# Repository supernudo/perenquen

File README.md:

# Perenquen

Robot de laberinto o micromouse.

Perenquén es mi primer robot de laberinto. Tiene una tracción diferencial de 4 ruedas diseñada para acelerar en recta a 10m/s/s y alcanza una velocidad de 3m/s. La posición de su centro de masa le permite hacer giros precisos sobre sus ruedas delanteras sin derrapar, a pesar de tener 4 ruedas. Para controlar su velocidad y posición utiliza encoders magnéticos. Durante las curvas utiliza un giroscopo para girar con precisión, independientemente de si derrapan las ruedas. Además, utiliza 4 sensores infrarrojos (2 delanteros y 2 diagonales) para navegar por el laberinto.

## Autor

Javier Baliñas Santos

## Licencia

Todos estos productos están liberados mediante [Creative Commons Attribution-ShareAlike 4.0 International License](http://creativecommons.org/licenses/by-sa/4.0/).  
*All these products are released under [Creative Commons Attribution-ShareAlike 4.0 International License](http://creativecommons.org/licenses/by-sa/4.0/).*

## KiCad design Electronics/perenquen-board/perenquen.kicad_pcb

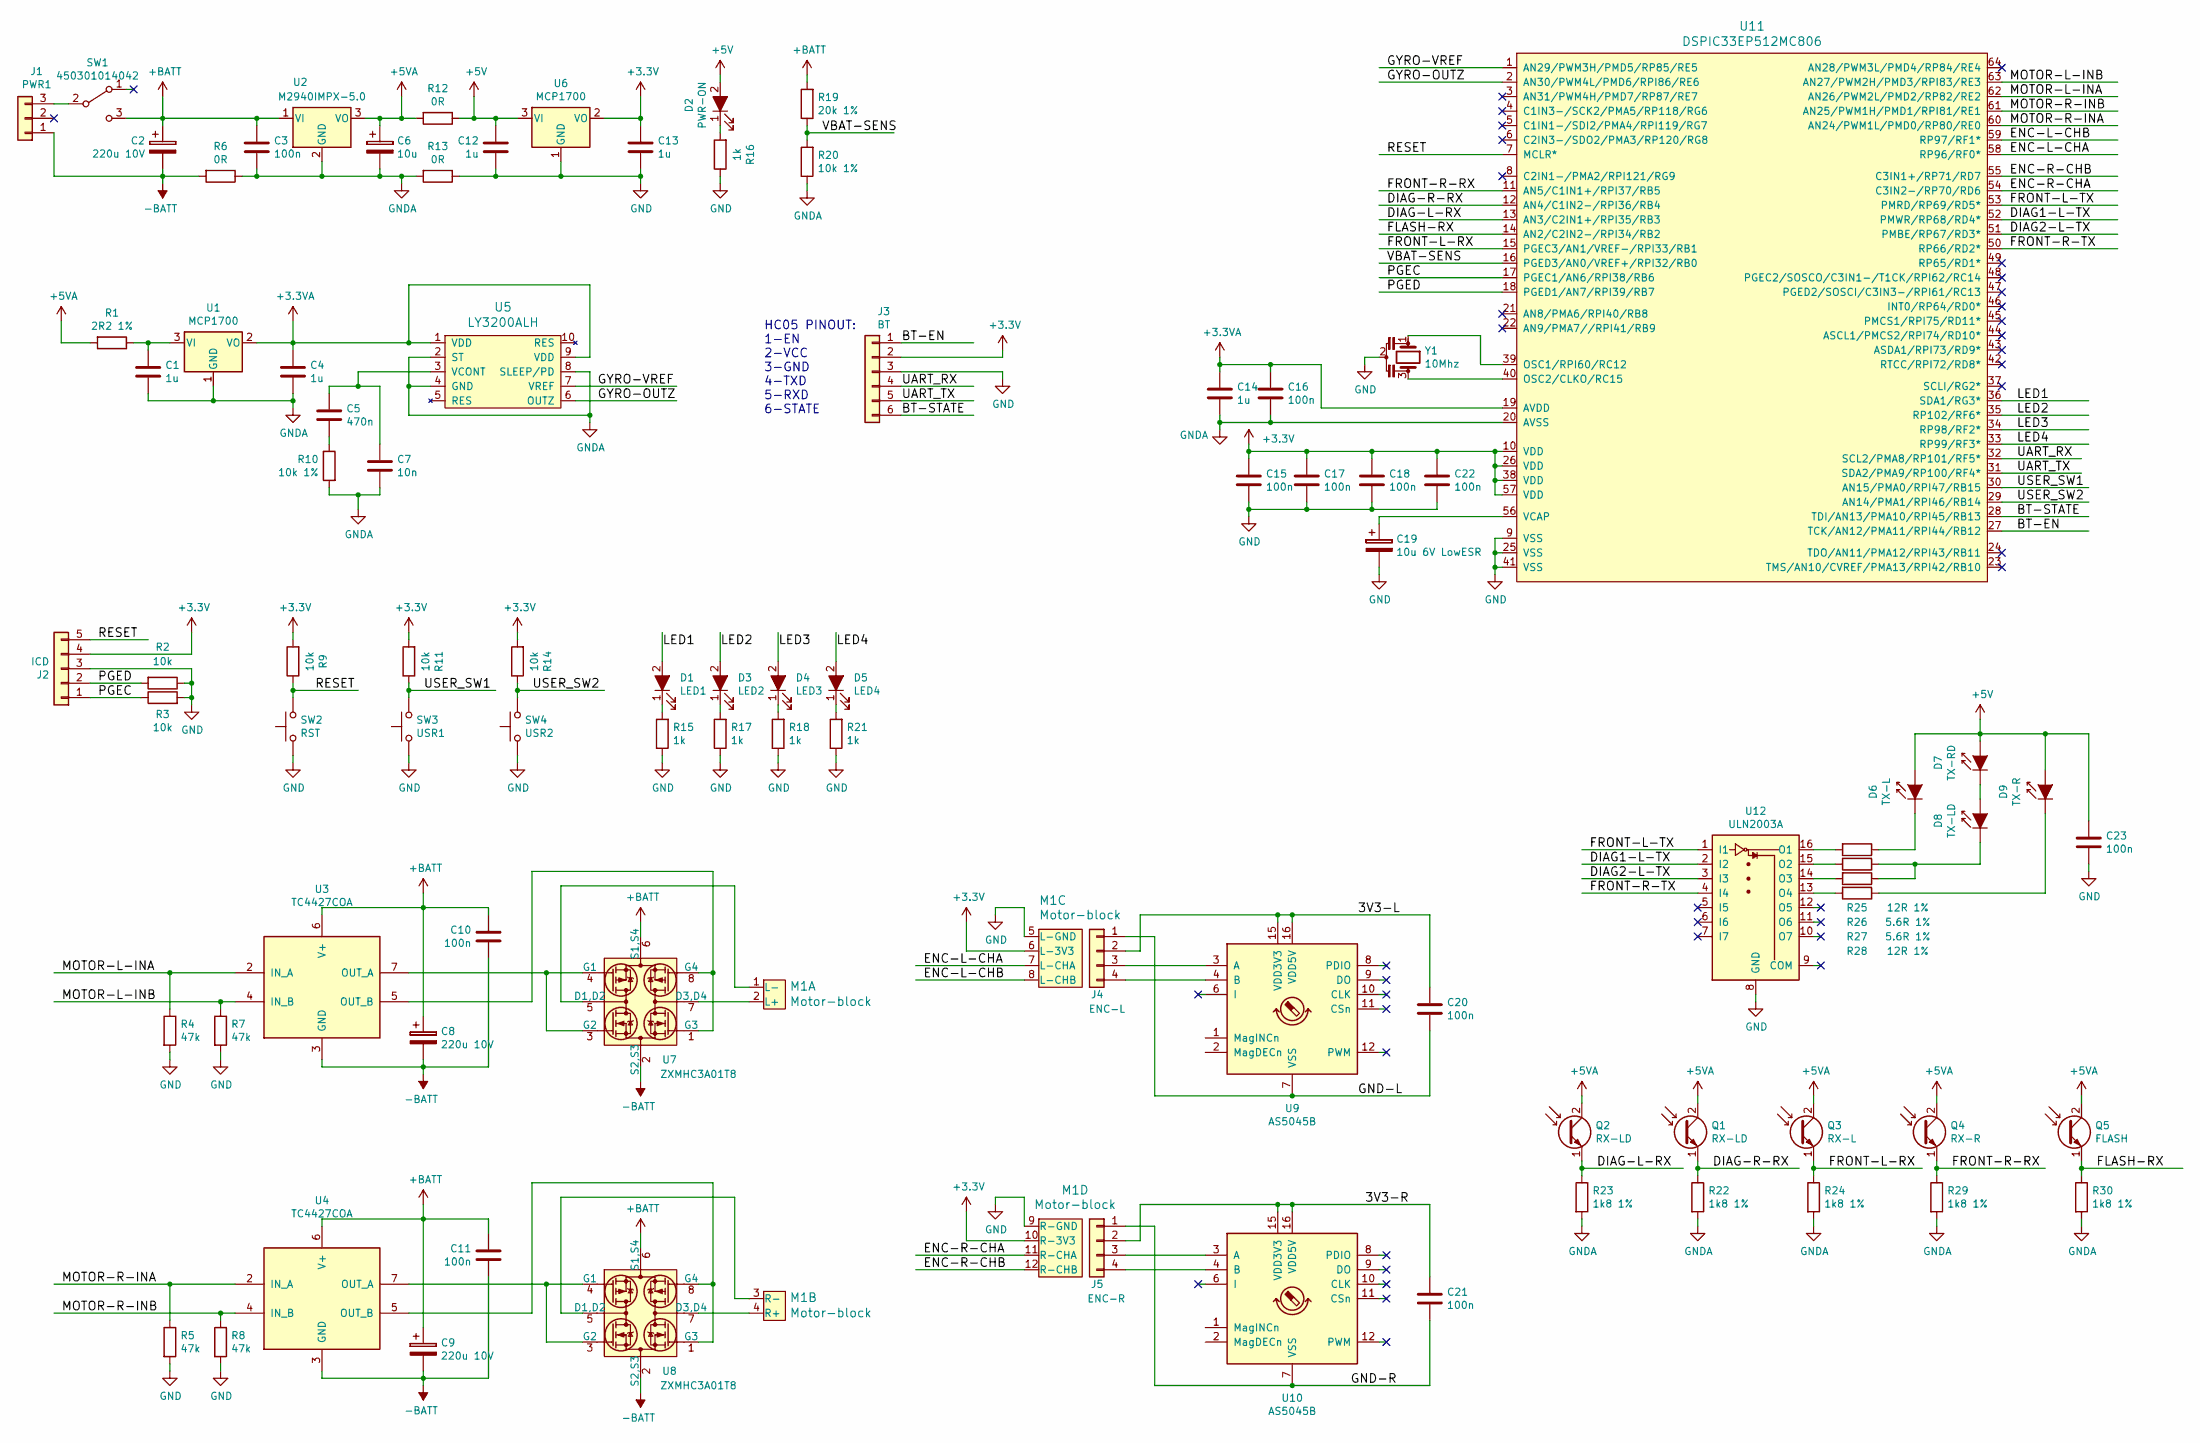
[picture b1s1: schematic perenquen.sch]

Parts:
C1, C4, C12, C13, C14: 1u; C_0805; MPN 08053G105ZAT2A
C2, C8, C9: 220u 10V; CP_Tantalum_Case-X_EIA-7343-43_Reflow; MPN T491D227K010AT
C3, C10, C11, C15, C16, C17, C18, C20, C21, C22, C23: 100n; C_0603; MPN 0603YC104KAT2A
C5: 470n; C_0603; MPN 0603YD474KAT2A
C6: 10u; C_0603; MPN T491C106M016AT
C7: 10n; C_0603; MPN 06035C103KAT2A
C19: 10u 6V LowESR; CP_Tantalum_Case-U_EIA-6032-15_Reflow; MPN T491C106M016AT
D1: LED1; D_0603; MPN SML-D12P8WT86
D2: PWR-ON; D_0603; MPN SML-D12V1WT86
D3: LED2; D_0603; MPN SML-D12P8WT86
D4: LED3; D_0603; MPN SML-D12P8WT86
D5: LED4; D_0603; MPN SML-D12P8WT86
D6: TX-L; LED_D5.0mm_Horizontal_O1.27mm_Z3.0mm; MPN SFH4545
D7: TX-RD; LED_D5.0mm_Horizontal_O1.27mm_Z3.0mm; MPN SFH4545
D8: TX-LD; LED_D5.0mm_Horizontal_O1.27mm_Z3.0mm; MPN SFH4545
D9: TX-R; LED_D5.0mm_Horizontal_O1.27mm_Z3.0mm; MPN SFH4545
J1: PWR1; JST_PH_B3B-PH-K_03x2.00mm_Straight; MPN B3B-PH-K-S(LF)(SN)
J2: ICD; Pin_Header_Angled_1x05_Pitch2.54mm; MPN 68016-410HLF
J3: BT; Socket_Strip_Straight_1x06_Pitch2.54mm; MPN 801-87-006-20-001101
J4: ENC-L; Pin_Header_Angled_1x04_Pitch2.54mm; MPN 68016-410HLF
J5: ENC-R; Pin_Header_Angled_1x04_Pitch2.54mm; MPN 68016-410HLF
M1: Motor-block; Perenquen-motor-block
Q1, Q2: RX-LD; LED_D3.0mm_Horizontal_O1.27mm_Z2.0mm; MPN TEFT4300
Q3: RX-L; LED_D3.0mm_Horizontal_O1.27mm_Z2.0mm; MPN TEFT4300
Q4: RX-R; LED_D3.0mm_Horizontal_O1.27mm_Z2.0mm; MPN TEFT4300
Q5: FLASH; LED_D3.0mm; MPN TEFT4300
R1: 2R2 1%; R_0603; MPN RC0603FR-072R2L
R2, R3, R9, R11, R14: 10k; R_0603; MPN RC0603FR-0710KL
R4, R5, R7, R8: 47k; R_0603; MPN RC0603JR-0747KL
R6, R12, R13: 0R; R_0805; MPN RC0805JR-070RL
R10, R20: 10k 1%; R_0603; MPN RC0603FR-0710KL
R15, R16, R17, R18, R21: 1k; R_0603; MPN RC0603JR-071KL
R19: 20k 1%; R_0603; MPN RC0603FR-0720KL
R22, R23, R24, R29, R30: 1k8 1%; R_0603; MPN RC0603FR-071K8L
R25, R28: 12R 1%; R_0805; MPN RC0805FR-0712RL
R26, R27: 5.6R 1%; R_0805; MPN RMCF0805FT5R60
SW1: 450301014042; Pin_Header_Straight_1x03_Pitch2.54mm; MPN 450301014042
SW2: RST; SW_SPST_B3U-1000P; MPN B3U-1000P
SW3: USR1; SW_SPST_B3U-1000P; MPN B3U-1000P
SW4: USR2; SW_SPST_B3U-1000P; MPN B3U-1000P
U1, U6: MCP1700; SOT-23; MPN MCP1700T-3302E/TT
U2: M2940IMPX-5.0; SOT-223-3_TabPin2; MPN LM2940IMPX-5.0/NOPB
U3, U4: TC4427COA; SOIC-8-N; MPN TC4427COA
U5: LY3200ALH; Gyro_ST_LGA10; MPN LY3200ALHTR
U7, U8: ZXMHC3A01T8; Zetex_SM8; MPN ZXMHC3A01T8TA
U9, U10: AS5045B; SSOP-16_5.3x6.2mm_Pitch0.65mm; MPN AS5045B
U11: DSPIC33EP512MC806; TQFP-64_10x10mm_Pitch0.5mm; MPN DSPIC33EP512MC806-I/PT
U12: ULN2003A; SSOP-16_4.4x5.2mm_Pitch0.65mm; MPN ULN2003APW
Y1: 10Mhz; Resonator_Murata_CSTCE_3pin; MPN CSTCE10M0G55-R0

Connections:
+3.3VA: C4.1, C14.1, C16.1, U1.2 (VO), U5.1 (VDD), U5.9 (VDD), U11.19 (AVDD)
+3V3: C13.1, C15.1, C17.1, C18.1, C22.1, J2.4, J3.2, M1.6 (L-3V3), M1.10 (R-3V3), R9.2, R11.2, R14.2, U6.2 (VO), U11.10 (VDD), U11.26 (VDD), U11.38 (VDD), U11.57 (VDD)
+5V: C12.1, C23.1, D2.2 (A), D6.2 (A), D7.2 (A), D9.2 (A), R12.1, U6.3 (VI)
+5VA: C6.1, Q1.2 (C), Q2.2 (C), Q3.2 (C), Q4.2 (C), Q5.2 (C), R1.2, R12.2, U2.3 (VO)
+BATT: C2.1, C3.1, C8.1, C9.1, C10.1, C11.1, R19.2, SW1.3 (C), U2.1 (VI), U3.6 (V+), U4.6 (V+), U7.6 (S1,S4), U8.6 (S1,S4)
-BATT: C2.2, C8.2, C9.2, C10.2, C11.2, J1.1, R6.2, U3.3 (GND), U4.3 (GND), U7.2 (S2,S3), U8.2 (S2,S3)
/3V3-L: C20.1, J4.2, U9.15 (VDD3V3), U9.16 (VDD5V)
/3V3-R: C21.1, J5.2, U10.15 (VDD3V3), U10.16 (VDD5V)
/BT-EN: J3.1, U11.27 (TCK/AN12/PMA11/RPI44/RB12)
/BT-STATE: J3.6, U11.28 (TDI/AN13/PMA10/RPI45/RB13)
/DIAG1-L-TX: U11.52 (PMWR/RP68/RD4*), U12.2 (I2)
/DIAG2-L-TX: U11.51 (PMBE/RP67/RD3*), U12.3 (I3)
/DIAG-L-RX: Q2.1 (E), R23.1, U11.13 (AN3/C2IN1+/RPI35/RB3)
/DIAG-R-RX: Q1.1 (E), R22.1, U11.12 (AN4/C1IN2-/RPI36/RB4)
/ENC-L-CHA: M1.7 (L-CHA), U11.58 (RP96/RF0*)
/ENC-L-CHB: M1.8 (L-CHB), U11.59 (RP97/RF1*)
/ENC-R-CHA: M1.11 (R-CHA), U11.54 (C3IN2-/RP70/RD6)
/ENC-R-CHB: M1.12 (R-CHB), U11.55 (C3IN1+/RP71/RD7)
/FLASH-RX: Q5.1 (E), R30.1, U11.14 (AN2/C2IN2-/RPI34/RB2)
/FRONT-L-RX: Q3.1 (E), R24.1, U11.15 (PGEC3/AN1/VREF-/RPI33/RB1)
/FRONT-L-TX: U11.53 (PMRD/RP69/RD5*), U12.1 (I1)
/FRONT-R-RX: Q4.1 (E), R29.1, U11.11 (AN5/C1IN1+/RPI37/RB5)
/FRONT-R-TX: U11.50 (RP66/RD2*), U12.4 (I4)
/GND-L: C20.2, J4.1, U9.7 (VSS)
/GND-R: C21.2, J5.1, U10.7 (VSS)
/GYRO-OUTZ: U5.6 (OUTZ), U11.2 (AN30/PWM4L/PMD6/RPI86/RE6)
/GYRO-VREF: U5.7 (VREF), U11.1 (AN29/PWM3H/PMD5/RP85/RE5)
/LED1: D1.2 (A), U11.36 (SDA1/RG3*)
/LED2: D3.2 (A), U11.35 (RP102/RF6*)
/LED3: D4.2 (A), U11.34 (RP98/RF2*)
/LED4: D5.2 (A), U11.33 (RP99/RF3*)
/MOTOR-L-INA: R4.1, U3.2 (IN_A), U11.62 (AN26/PWM2L/PMD2/RP82/RE2)
/MOTOR-L-INB: R7.1, U3.4 (IN_B), U11.63 (AN27/PWM2H/PMD3/RPI83/RE3)
/MOTOR-R-INA: R5.1, U4.2 (IN_A), U11.60 (AN24/PWM1L/PMD0/RP80/RE0)
/MOTOR-R-INB: R8.1, U4.4 (IN_B), U11.61 (AN25/PWM1H/PMD1/RPI81/RE1)
/PGEC: J2.1, R3.1, U11.17 (PGEC1/AN6/RPI38/RB6)
/PGED: J2.2, R2.2, U11.18 (PGED1/AN7/RPI39/RB7)
/RESET: J2.5, R9.1, SW2.2, U11.7 (MCLR*)
/UART_RX: J3.4, U11.32 (SCL2/PMA8/RP101/RF5*)
/UART_TX: J3.5, U11.31 (SDA2/PMA9/RP100/RF4*)
/USER_SW1: R11.1, SW3.2, U11.30 (AN15/PMA0/RPI47/RB15)
/USER_SW2: R14.1, SW4.2, U11.29 (AN14/PMA1/RPI46/RB14)
/VBAT-SENS: R19.1, R20.2, U11.16 (PGED3/AN0/VREF+/RPI32/RB0)
GND: C12.2, C13.2, C15.2, C17.2, C18.2, C19.2, C22.2, C23.2, J2.3, J3.3, M1.5 (L-GND), M1.9 (R-GND), R2.1, R3.2, R4.2, R5.2, R7.2, R8.2, R13.1, R15.1, R16.1, R17.1, R18.1, R21.1, SW2.1, SW3.1, SW4.1, U6.1 (GND), U11.9 (VSS), U11.25 (VSS), U11.41 (VSS), U12.8 (GND), Y1.2
GNDA: C1.2, C3.2, C4.2, C6.2, C7.2, C14.2, C16.2, R6.1, R10.2, R13.2, R20.1, R22.2, R23.2, R24.2, R29.2, R30.2, U1.1 (GND), U2.2 (GND), U5.2 (ST), U5.4 (GND), U5.8 (SLEEP/PD), U11.20 (AVSS)
unnamed: C1.1, R1.1, U1.3 (VI)
unnamed: C5.1, C7.1, U5.3 (VCONT)
unnamed: C5.2, R10.1
unnamed: C19.1, U11.56 (VCAP)
unnamed: D1.1 (K), R15.2
unnamed: D2.1 (K), R16.2
unnamed: D3.1 (K), R17.2
unnamed: D4.1 (K), R18.2
unnamed: D5.1 (K), R21.2
unnamed: D6.1 (K), R25.1
unnamed: D7.1 (K), D8.2 (A)
unnamed: D8.1 (K), R26.1, R27.1
unnamed: D9.1 (K), R28.1
unnamed: J1.3, SW1.2 (B)
unnamed: J4.3, U9.3 (A)
unnamed: J4.4, U9.4 (B)
unnamed: J5.3, U10.3 (A)
unnamed: J5.4, U10.4 (B)
unnamed: M1.1 (L-), U7.5 (D1,D2)
unnamed: M1.2 (L+), U7.7 (D3,D4)
unnamed: M1.3 (R-), U8.5 (D1,D2)
unnamed: M1.4 (R+), U8.7 (D3,D4)
unnamed: R25.2, U12.16 (O1)
unnamed: R26.2, U12.15 (O2)
unnamed: R27.2, U12.14 (O3)
unnamed: R28.2, U12.13 (O4)
unnamed: U3.5 (OUT_B), U7.1 (G3), U7.8 (G4)
unnamed: U3.7 (OUT_A), U7.3 (G2), U7.4 (G1)
unnamed: U4.5 (OUT_B), U8.1 (G3), U8.8 (G4)
unnamed: U4.7 (OUT_A), U8.3 (G2), U8.4 (G1)
unnamed: U11.39 (OSC1/RPI60/RC12), Y1.1
unnamed: U11.40 (OSC2/CLKO/RC15), Y1.3

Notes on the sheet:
HC05 PINOUT: 1-EN 2-VCC 3-GND 4-TXD 5-RXD 6-STATE

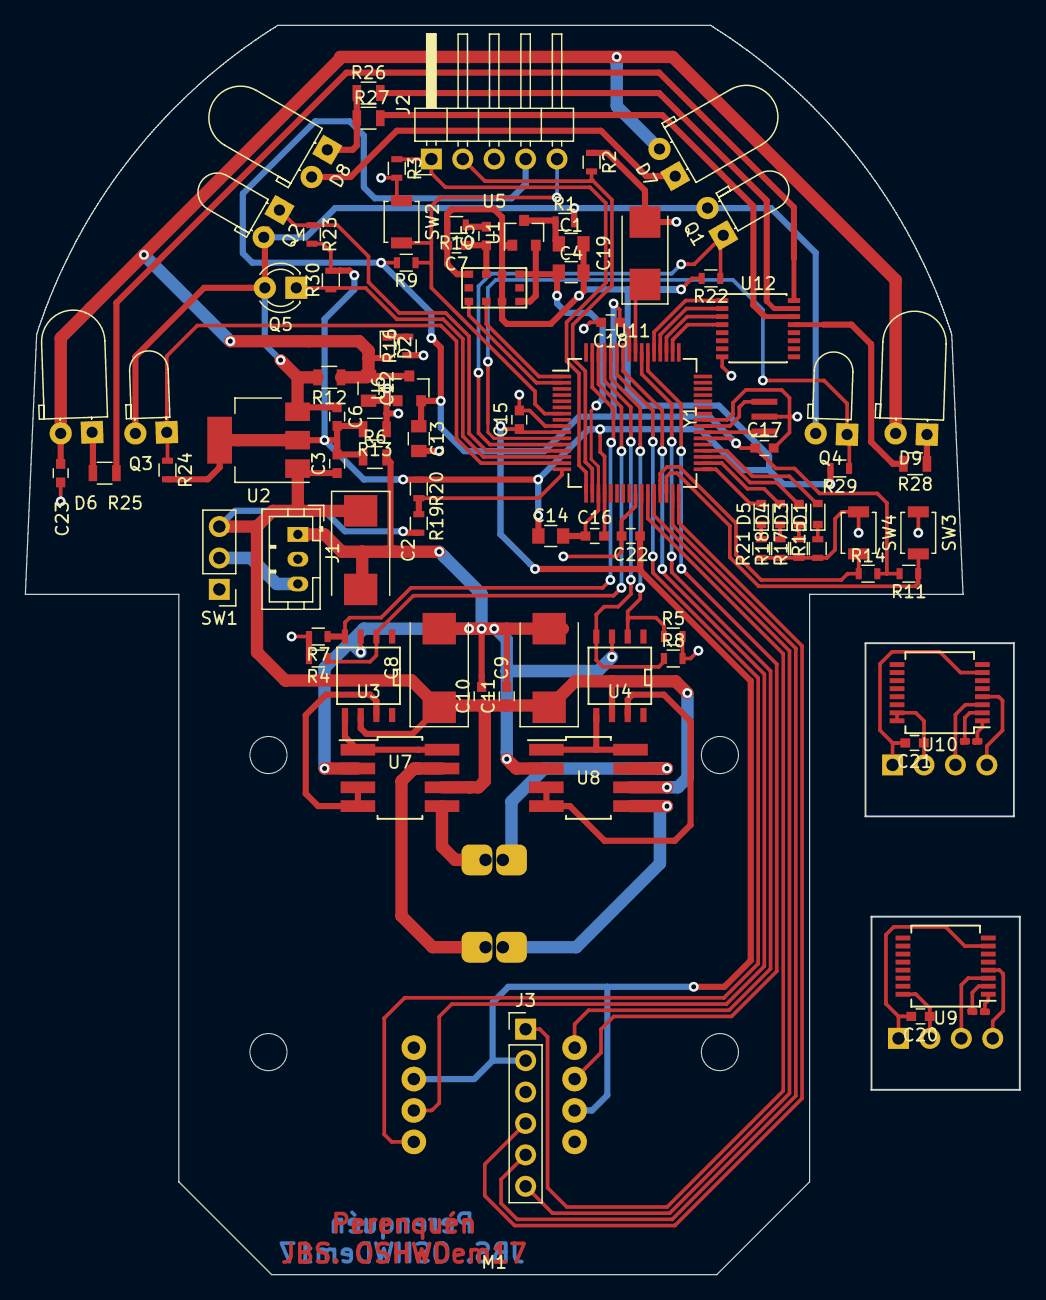
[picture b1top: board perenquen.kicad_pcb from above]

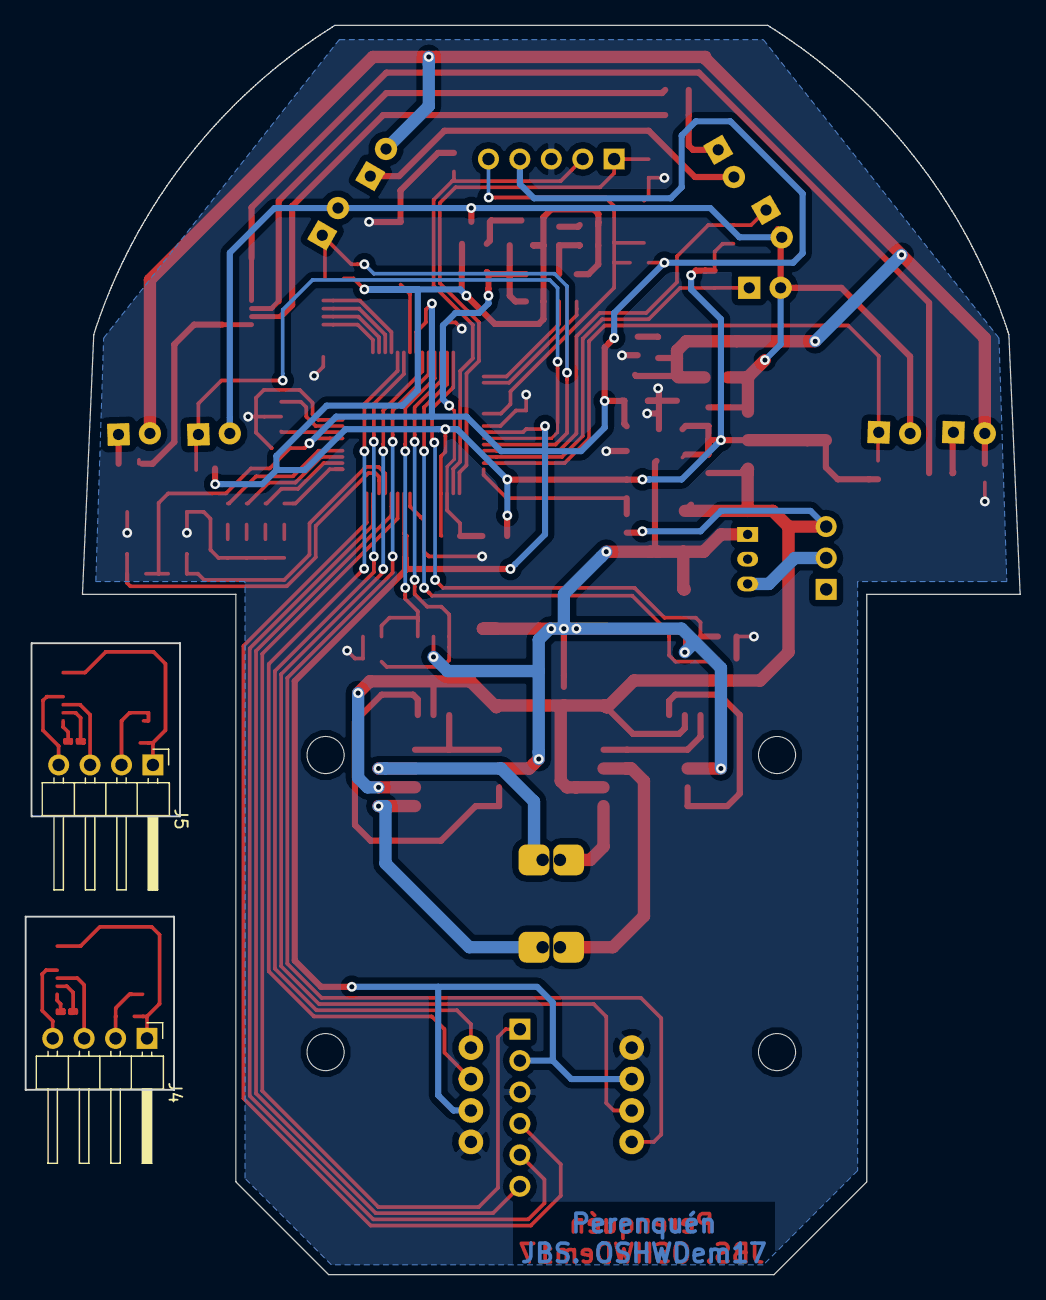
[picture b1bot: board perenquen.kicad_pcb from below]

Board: 2 copper layers, 80.4 x 101.0 mm, 90 parts (2 on the bottom side), 77 nets.

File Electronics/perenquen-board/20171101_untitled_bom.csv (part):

Qty,Line Item,Manufacturer,MPN,Octopart URL,Schematic Reference,Internal Part Number,Description,Total Qty (@ Batch Size: 1),SKU,SKU,SKU,SKU,Packaging,Packaging,Packaging,Packaging,Unit Price (@ Batch Size: 1),Unit Price (@ Batch Size: 1),Unit Price (@ Batch Size: 1),Unit Price (@ Batch Size: 1),In Stock,In Stock,In Stock,In Stock,MOQ,MOQ,MOQ,MOQ,URL,URL,URL,URL,Distributor [Digi-Key],SKU [Digi-Key],Packaging [Digi-Key],Unit Price (@ Batch Size: 1) [Digi-Key],Line Total [Digi-Key],Batch Total [Digi-Key],In Stock [Digi-Key],MOQ [Digi-Key],URL [Digi-Key],Notes
,,,,,,,,,Digi-Key,Farnell,RS Components,TME,Digi-Key,Farnell,RS Components,TME,Digi-Key,Farnell,RS Components,TME,Digi-Key,Farnell,RS Components,TME,Digi-Key,Farnell,RS Components,TME,Digi-Key,Farnell,RS Components,TME,,,,,,,,,,
3,T491D227K010AT,KEMET,T491D227K010AT,https://octopart.com/t491d227k010at-kemet-87914,C2 C9 C8,,220u 10V,3,399-8379-1-ND,1310127,,T491D227K010AT,Cut Tape,,,,1.34880898,1.17,,0.5695066706,2523,263,,19,1,1,,2,https://octopart.com/click/track?country=ES&ak=68b25f31&sig=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,https://octopart.com/click/track?country=ES&ak=68b25f31&sig=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,,https://octopart.com/click/track?country=ES&ak=68b25f31&sig=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,Digi-Key,399-8379-1-ND,Cut Tape,1.34880898,4.04642694,4.04642694,2523,1,https://octopart.com/click/track?country=ES&ak=68b25f31&sig=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,
11,0603YC104KAT2A,AVX,0603YC104KAT2A,https://octopart.com/0603yc104kat2a-avx-55386347,C3 C11 C10 C23 C20 C21 C17 C18 C22 C15 C16,,100n,11,478-1239-1-ND,2367633,,0603YC104KAT2A,Cut Tape,Cut Tape,,,0.020618736000000002,3,,,1493489,44562,,102600,1,1,,100,https://octopart.com/click/track?country=ES&ak=68b25f31&sig=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,https://octopart.com/click/track?country=ES&ak=68b25f31&sig=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,,https://octopart.com/click/track?country=ES&ak=68b25f31&sig=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,Digi-Key,478-1239-1-ND,Cut Tape,0.020618736000000002,0.226806096,0.226806096,1493489,1,https://octopart.com/click/track?country=ES&ak=68b25f31&sig=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,
1,T491C106M016AT,KEMET,T491C106M016AT,https://octopart.com/t491c106m016at-kemet-219788,C6,,10u,1,399-3735-1-ND,2462774,,T491C106M016AT,Cut Tape,,,,0.52405954,723,,,50675,607,,110,1,1,,5,https://octopart.com/click/track?country=ES&ak=68b25f31&sig=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,https://octopart.com/click/track?country=ES&ak=68b25f31&sig=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,,https://octopart.com/click/track?country=ES&ak=68b25f31&sig=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,Digi-Key,399-3735-1-ND,Cut Tape,0.52405954,0.52405954,0.52405954,50675,1,https://octopart.com/click/track?country=ES&ak=68b25f31&sig=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,
5,08053G105ZAT2A,AVX,08053G105ZAT2A,https://octopart.com/08053g105zat2a-avx-194975,C12 C1 C13 C4 C14,,1u,5,478-1426-1-ND,2332746,,08053G105ZAT2A,Cut Tape,,,,0.28350762,,,,25647,790,,6701,1,10,,100,https://octopart.com/click/track?country=ES&ak=68b25f31&sig=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,https://octopart.com/click/track?country=ES&ak=68b25f31&sig=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,,https://octopart.com/click/track?country=ES&ak=68b25f31&sig=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,Digi-Key,478-1426-1-ND,Cut Tape,0.28350762,1.4175381,1.4175381,25647,1,https://octopart.com/click/track?country=ES&ak=68b25f31&sig=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,
1,06035C103KAT2A,AVX,06035C103KAT2A,https://octopart.com/06035c103kat2a-avx-55386346,C7,,10n,1,478-1227-1-ND,1327675,,06035C103KAT2A,Cut Tape,,,,0.08591140000000001,,,,896093,89871,,100000,1,10,,100,https://octopart.com/click/track?country=ES&ak=68b25f31&sig=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,https://octopart.com/click/track?country=ES&ak=68b25f31&sig=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,,https://octopart.com/click/track?country=ES&ak=68b25f31&sig=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,Digi-Key,478-1227-1-ND,Cut Tape,0.08591140000000001,0.08591140000000001,0.08591140000000001,896093,1,https://octopart.com/click/track?country=ES&ak=68b25f31&sig=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,
1,0603YD474KAT2A,AVX,0603YD474KAT2A,https://octopart.com/0603yd474kat2a-avx-194840,C5,,470n,1,478-1248-1-ND,2367636,,0603YD474KAT2A,Cut Tape,Cut Tape,,,0.20618736000000001,0.25,,,29454,1474,,6000,1,1,,100,https://octopart.com/click/track?country=ES&ak=68b25f31&sig=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,https://octopart.com/click/track?country=ES&ak=68b25f31&sig=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,,https://octopart.com/click/track?country=ES&ak=68b25f31&sig=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,Digi-Key,478-1248-1-ND,Cut Tape,0.20618736000000001,0.20618736000000001,0.20618736000000001,29454,1,https://octopart.com/click/track?country=ES&ak=68b25f31&sig=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,
1,T491C106M016AT,KEMET,T491C106M016AT,https://octopart.com/t491c106m016at-kemet-219788,C19,,10u 6V LowESR,1,399-3735-1-ND,2462774,,T491C106M016AT,Cut Tape,,,,0.52405954,723,,,50675,607,,110,1,1,,5,https://octopart.com/click/track?country=ES&ak=68b25f31&sig=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,https://octopart.com/click/track?country=ES&ak=68b25f31&sig=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,,https://octopart.com/click/track?country=ES&ak=68b25f31&sig=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,Digi-Key,399-3735-1-ND,Cut Tape,0.52405954,0.52405954,0.52405954,50675,1,https://octopart.com/click/track?country=ES&ak=68b25f31&sig=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,
1,SML-D12V1WT86,Rohm,SML-D12V1WT86,https://octopart.com/sml-d12v1wt86-rohm-70837113,D2,,PWR-ON,1,SML-D12V1WT86CT-ND,,,,Cut Tape,,,,0.18900508000000002,,,,16219,,,,1,,,,https://octopart.com/click/track?country=ES&ak=68b25f31&sig=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,,,,Digi-Key,SML-D12V1WT86CT-ND,Cut Tape,0.18900508000000002,0.18900508000000002,0.18900508000000002,16219,1,https://octopart.com/click/track?country=ES&ak=68b25f31&sig=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,
1,SFH4545,Osram Opto,SFH 4545,https://octopart.com/sfh+4545-osram+opto-31094092,D6,,TX-L,1,475-2919-ND,,,SFH4545,Bulk,,,,0.6443355000000001,,,0.48651625820000005,54630,,,1034,1,,,1,https://octopart.com/click/track?country=ES&ak=68b25f31&sig=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,,,https://octopart.com/click/track?country=ES&ak=68b25f31&sig=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,Digi-Key,475-2919-ND,Bulk,0.6443355000000001,0.6443355000000001,0.6443355000000001,54630,1,https://octopart.com/click/track?country=ES&ak=68b25f31&sig=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,
2,SFH4545,Osram Opto,SFH 4545,https://octopart.com/sfh+4545-osram+opto-31094092,D7 D8,,TX-LD,2,475-2919-ND,,,SFH4545,Bulk,,,,0.6443355000000001,,,0.48651625820000005,54630,,,1034,1,,,1,https://octopart.com/click/track?country=ES&ak=68b25f31&sig=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,,,https://octopart.com/click/track?country=ES&ak=68b25f31&sig=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,Digi-Key,475-2919-ND,Bulk,0.6443355000000001,1.2886710000000001,1.2886710000000001,54630,1,https://octopart.com/click/track?country=ES&ak=68b25f31&sig=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,
1,SFH4545,Osram Opto,SFH 4545,https://octopart.com/sfh+4545-osram+opto-31094092,D9,,TX-R,1,475-2919-ND,,,SFH4545,Bulk,,,,0.6443355000000001,,,0.48651625820000005,54630,,,1034,1,,,1,https://octopart.com/click/track?country=ES&ak=68b25f31&sig=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,,,https://octopart.com/click/track?country=ES&ak=68b25f31&sig=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,Digi-Key,475-2919-ND,Bulk,0.6443355000000001,0.6443355000000001,0.6443355000000001,54630,1,https://octopart.com/click/track?country=ES&ak=68b25f31&sig=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,
1,SML-D12P8WT86,Rohm,SML-D12P8WT86,https://octopart.com/sml-d12p8wt86-rohm-9289138,D1,,LED1,1,511-1579-1-ND,2507529,,,Cut Tape,,,,0.29209876,1.44,,,25783,4204,,,1,1,,,https://octopart.com/click/track?country=ES&ak=68b25f31&sig=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,https://octopart.com/click/track?country=ES&ak=68b25f31&sig=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,,,Digi-Key,511-1579-1-ND,Cut Tape,0.29209876,0.29209876,0.29209876,25783,1,https://octopart.com/click/track?country=ES&ak=68b25f31&sig=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,
1,SML-D12P8WT86,Rohm,SML-D12P8WT86,https://octopart.com/sml-d12p8wt86-rohm-9289138,D3,,LED2,1,511-1579-1-ND,2507529,,,Cut Tape,,,,0.29209876,1.44,,,25783,4204,,,1,1,,,https://octopart.com/click/track?country=ES&ak=68b25f31&sig=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,https://octopart.com/click/track?country=ES&ak=68b25f31&sig=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,,,Digi-Key,511-1579-1-ND,Cut Tape,0.29209876,0.29209876,0.29209876,25783,1,https://octopart.com/click/track?country=ES&ak=68b25f31&sig=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,
1,SML-D12P8WT86,Rohm,SML-D12P8WT86,https://octopart.com/sml-d12p8wt86-rohm-9289138,D4,,LED3,1,511-1579-1-ND,2507529,,,Cut Tape,,,,0.29209876,1.44,,,25783,4204,,,1,1,,,https://octopart.com/click/track?country=ES&ak=68b25f31&sig=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,https://octopart.com/click/track?country=ES&ak=68b25f31&sig=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,,,Digi-Key,511-1579-1-ND,Cut Tape,0.29209876,0.29209876,0.29209876,25783,1,https://octopart.com/click/track?country=ES&ak=68b25f31&sig=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,
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
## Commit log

2017-10-14 Some design notes and almost the mechanic design done
2017-10-17 Some improvements on gearbox support
2017-10-22 Added screw and nut holes to the main support. Created motor assembly with PCB pins
2017-10-24 Added preliminary perenquen-board
2017-10-25 Almost all main ICs
2017-10-28 [MECH] Created manufacture STL parts. [HW] All ICs included on sch. Some functional blocks done.
2017-10-29 Almost ready for PCB layout
2017-11-01 [SCH][BOM] Done. [PCB][FOOTPRINTS] In progress
2017-11-02 Almos ready for PCB layout. Some footprints error after loadding netlist
2017-11-03 [PCB] Mechanical parts placement done
2017-11-04 [PCB] H-bridges done
2017-11-04 [PCB] All parts groups placed and partialy routed
2017-11-05 [PCB] Design done
2017-11-05 [PCB] Generated manufacture files
2017-11-05 [PCB] Added edge cuts gerber file
2017-12-26 Minor changes (I think)
2018-10-04 [MECH] New parts organization. New motor block assembly in progress.
2018-10-06 [MECH] First version of gearbox supports recovered from OSWHDem17 branch
2018-10-07 [MECH] Assemblies has been updated. Added robot assemby and perequen boards 3d models
2018-10-07 Uncommited minor changes
2018-11-03 [SW] Added source code from P.Tinto robot.
2018-11-04 [FW] Removed NA code, firts compilation. [FW][ENCODERS] Right is workinkg, left seems to have a pin contact issue.
2018-11-04 [FW] HW validation done. All HW is working, even the gyro :-). It's been necesary to solder some vias/pads again and change the gain of one diagonal sensors. Take with care, if robot crash don't trus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
2018-11-04 [SW] HS PWM module driver done and working. Motor PWM test command updated with new driver.
2018-11-04 [SW] Set physical dimension stuff.
2018-11-06 [SW] Sensors aquisition in progress....
2018-11-08 [SW] Sensors working
2018-11-09 [FW] PD tunning in progress...
2018-11-10 [SW] CS stuff
2018-11-10 Wall tracker working for left side
2018-11-10 [SW] Turn bub fixed
2018-11-10 [SW] Added strat confs in comments
2018-11-19 [SW] FIX wall tracker bug
2019-04-09 [PYTHON][CMD] Tune command improvements [CMDLINE] Added echo command, goto telemetry improvements. [FIX][CMD] Sensors show bug [CS] Period now is 1ms, added pin debug traces. New cs debug function. [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
2019-04-11 [NEW] Telemetry module.
2019-04-14 [PYTHON][CMD] Added support for RFCOMM connection directly instead of pass thru serial. [TELEMETRY][FIXME] 1ms data rate not supported by HC-05. Tests with UART cable works perfectly.
2019-04-16 [TELEMETRY] A preliminary data reception is working.
2019-11-03 Added BOM used in PCBA. Kicad project migrated to Kicad 5.99.
2019-11-03 Updated design notes.
2019-11-03 [BT][LOGS] Added a bunch of test scritps for BT throuhtput research.
2019-11-03 [FW] Battery monitoring moved to ledd toggle event. [FW] Left motor driver go away. Motor PWM set commented (PWM disabled). [FW] Added some data telemetry test code.
2019-11-03 [LIBS] Update
2019-11-03 Minor changes
2019-11-03 [HW][FIX] Motor was burned [FW][TELEMETRY] Period set to 3ms (3xTs) [FW] PWM is set to 0 if low battery
2019-11-03 [FW] BT is disabled if low battery. [FW][TODO] Detect low battery with several samples.
2019-11-05 PWM polarity inverved
2019-11-07 Low battery threshold set to 5 seconds. PWM polarity inverted is working. New acc, speed and cs gains (TBT)
2019-11-08 [TEST] Works fine with start gain 30.
2024-09-29 Got host compilaton, robot simulator and display.
    XXX: Scheduler host does not support 250us period, set to 1ms. Time base set to 10ms.
    FIXME: gound field blocking simulation. Disabled.
2024-10-01 New display in progress
2024-10-03 Display simulator based on MMSIM examples is working. Cmd folder renamed to script.
2024-10-05 Update git ignore file. Removed deprecated file
2024-10-05 Kicad project updated to v8.0
2024-10-06 New ADC sensor reading sequence in progress.
2024-10-06 Refactored ADC sensor aquisition. Code review and house keeping.
    - Removed deprecated Eurobot code from main
    - TODO: review strat files
    - Moved LEDS, battery, HC05 and MCU setup functions to specific files
    - Reviewed main files. Spread some main.h code to more convenient files.
2024-10-06 Updated aversive4dspic
2024-10-07 Added LEDs supports. Two types, front and side LEDs
2024-10-07 Added stl files of LEDs supports
